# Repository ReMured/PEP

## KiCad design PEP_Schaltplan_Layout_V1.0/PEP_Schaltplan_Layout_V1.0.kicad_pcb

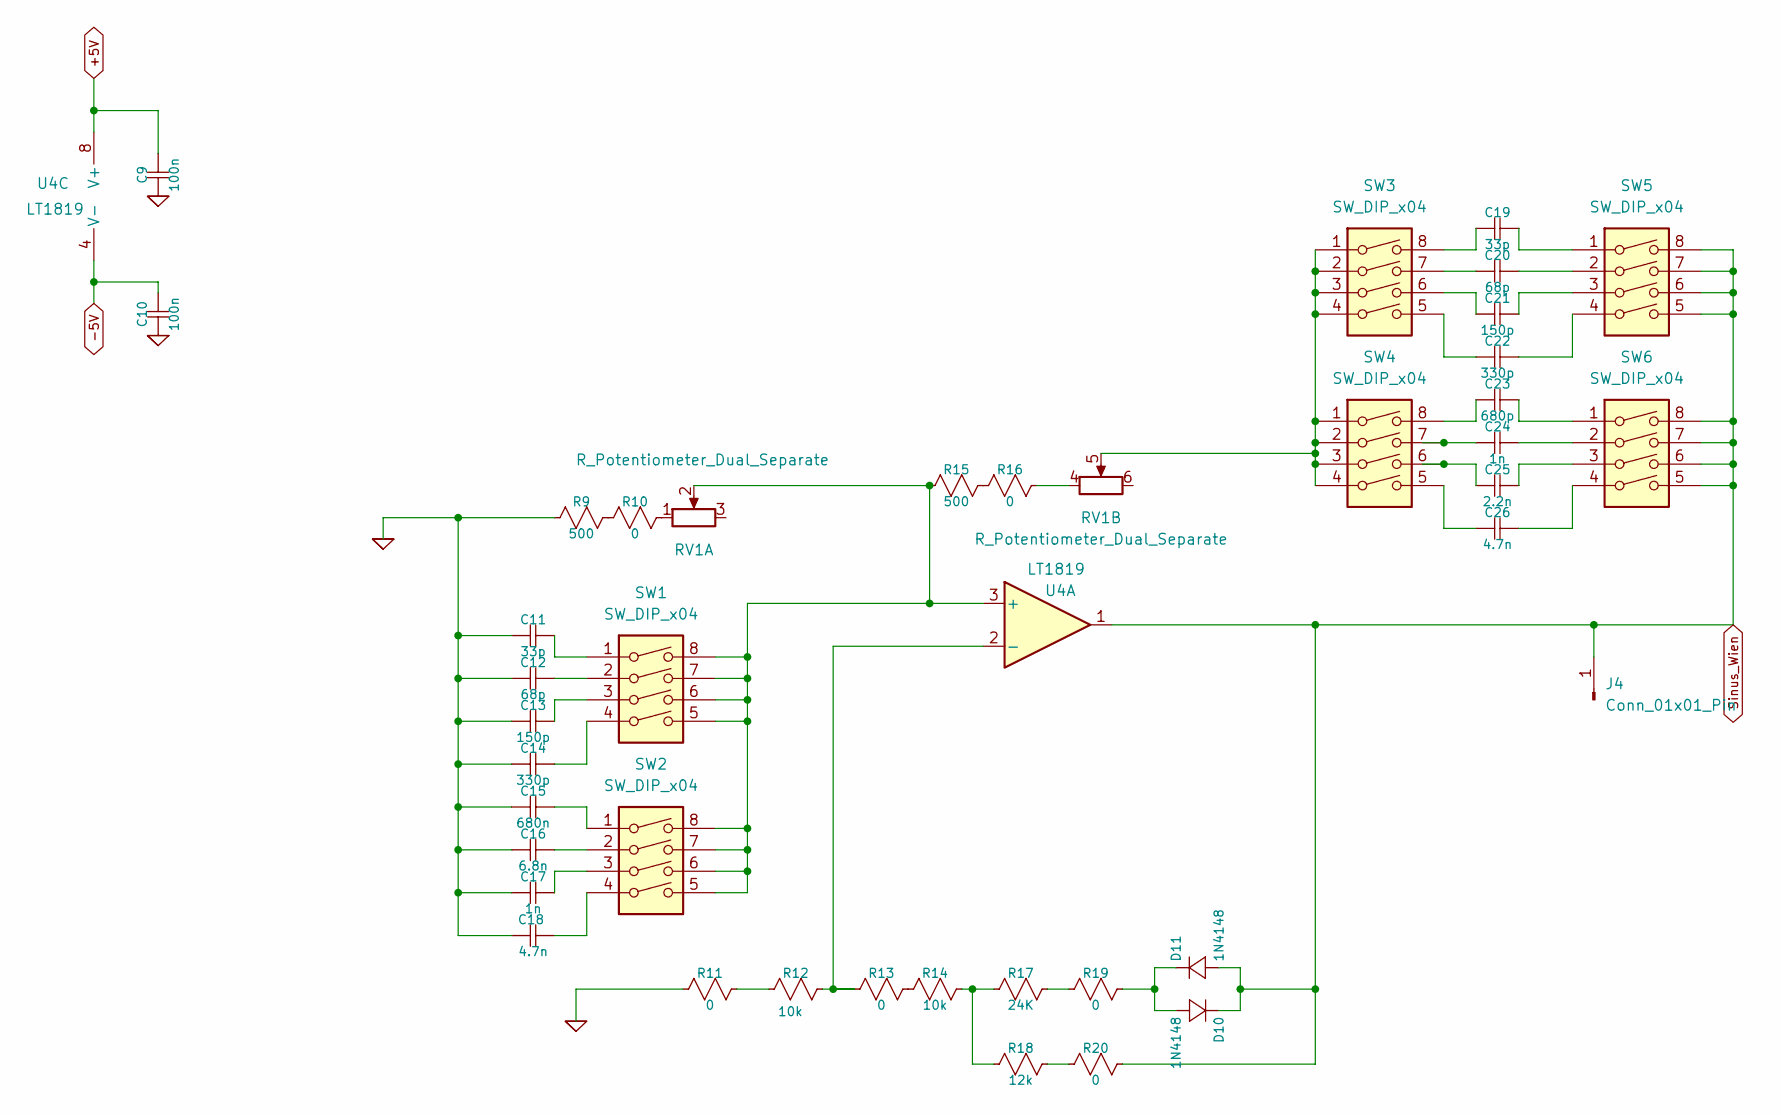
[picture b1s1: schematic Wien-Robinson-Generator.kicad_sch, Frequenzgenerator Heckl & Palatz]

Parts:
C9, C10: 100n; C_1206_3216Metric
C11, C19: 33p; C_1206_3216Metric
C12, C20: 68p; C_1206_3216Metric
C13, C21: 150p; C_1206_3216Metric
C14, C22: 330p; C_1206_3216Metric
C15: 680n; C_1206_3216Metric
C16: 6.8n; C_1206_3216Metric
C17, C24: 1n; C_1206_3216Metric
C18, C26: 4.7n; C_1206_3216Metric
C23: 680p; C_1206_3216Metric
C25: 2.2n; C_1206_3216Metric
D10, D11: 1N4148; D_DO-41_SOD81_P10.16mm_Horizontal
J4: Conn_01x01_Pin; PinSocket_1x01_P2.54mm_Vertical
R9, R15: 500; R_1206_3216Metric
R10, R11, R13, R16, R19, R20: 0; R_1206_3216Metric
R12, R14: 10k; R_1206_3216Metric
R17: 24K; R_1206_3216Metric
R18: 12k; R_1206_3216Metric
RV1: R_Potentiometer_Dual_Separate; Potentiometer_Piher_T-16H_Double_Horizontal
SW1, SW2, SW3, SW4, SW5, SW6: SW_DIP_x04; SW_DIP_SPSTx04_Slide_6.7x11.72mm_W7.62mm_P2.54mm_LowProfile
U4: LT1819; SO-8_3.9x4.9mm_P1.27mm

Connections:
+5V: C9.1, U4.8 (V+); also elsewhere on the board
-5V: C10.1, U4.4 (V-); also elsewhere on the board
GND: C9.2, C10.2, C11.2, C12.2, C13.2, C14.2, C15.2, C16.2, C17.2, C18.2, R9.2, R11.2; also elsewhere on the board
unnamed: C11.1, SW1.1
unnamed: C12.1, SW1.2
unnamed: C13.1, SW1.3
unnamed: C14.1, SW1.4
unnamed: C15.1, SW2.1
unnamed: C16.1, SW2.2
unnamed: C17.1, SW2.3
unnamed: C18.1, SW2.4
unnamed: C19.1, SW5.1
unnamed: C19.2, SW3.8
unnamed: C20.1, SW5.2
unnamed: C20.2, SW3.7
unnamed: C21.1, SW5.3
unnamed: C21.2, SW3.6
unnamed: C22.1, SW5.4
unnamed: C22.2, SW3.5
unnamed: C23.1, SW6.1
unnamed: C23.2, SW4.8
unnamed: C24.1, SW6.2
unnamed: C24.2, SW4.7
unnamed: C25.1, SW6.3
unnamed: C25.2, SW4.6
unnamed: C26.1, SW6.4
unnamed: C26.2, SW4.5
unnamed: D10.1 (+), D11.2 (-), R19.1
unnamed: R10.1, RV1.1
unnamed: R9.1, R10.2
unnamed: R11.1, R12.2
unnamed: R13.1, R14.2
unnamed: R14.1, R17.2, R18.2
unnamed: R15.1, R16.2
unnamed: R16.1, RV1.4
unnamed: R17.1, R19.2
unnamed: R18.1, R20.2
unnamed: RV1.5, SW3.1, SW3.2, SW3.3, SW3.4, SW4.1, SW4.2, SW4.3, SW4.4
unnamed: R15.2, RV1.2, SW1.5, SW1.6, SW1.7, SW1.8, SW2.5, SW2.6, SW2.7, SW2.8, U4.3 (+)
unnamed: R12.1, R13.2, U4.2 (-)
Sinus_Wien: D10.2 (-), D11.1 (+), J4.1 (Pin_1_1), R20.1, SW5.5, SW5.6, SW5.7, SW5.8, SW6.5, SW6.6, SW6.7, SW6.8, U4.1; also elsewhere on the board

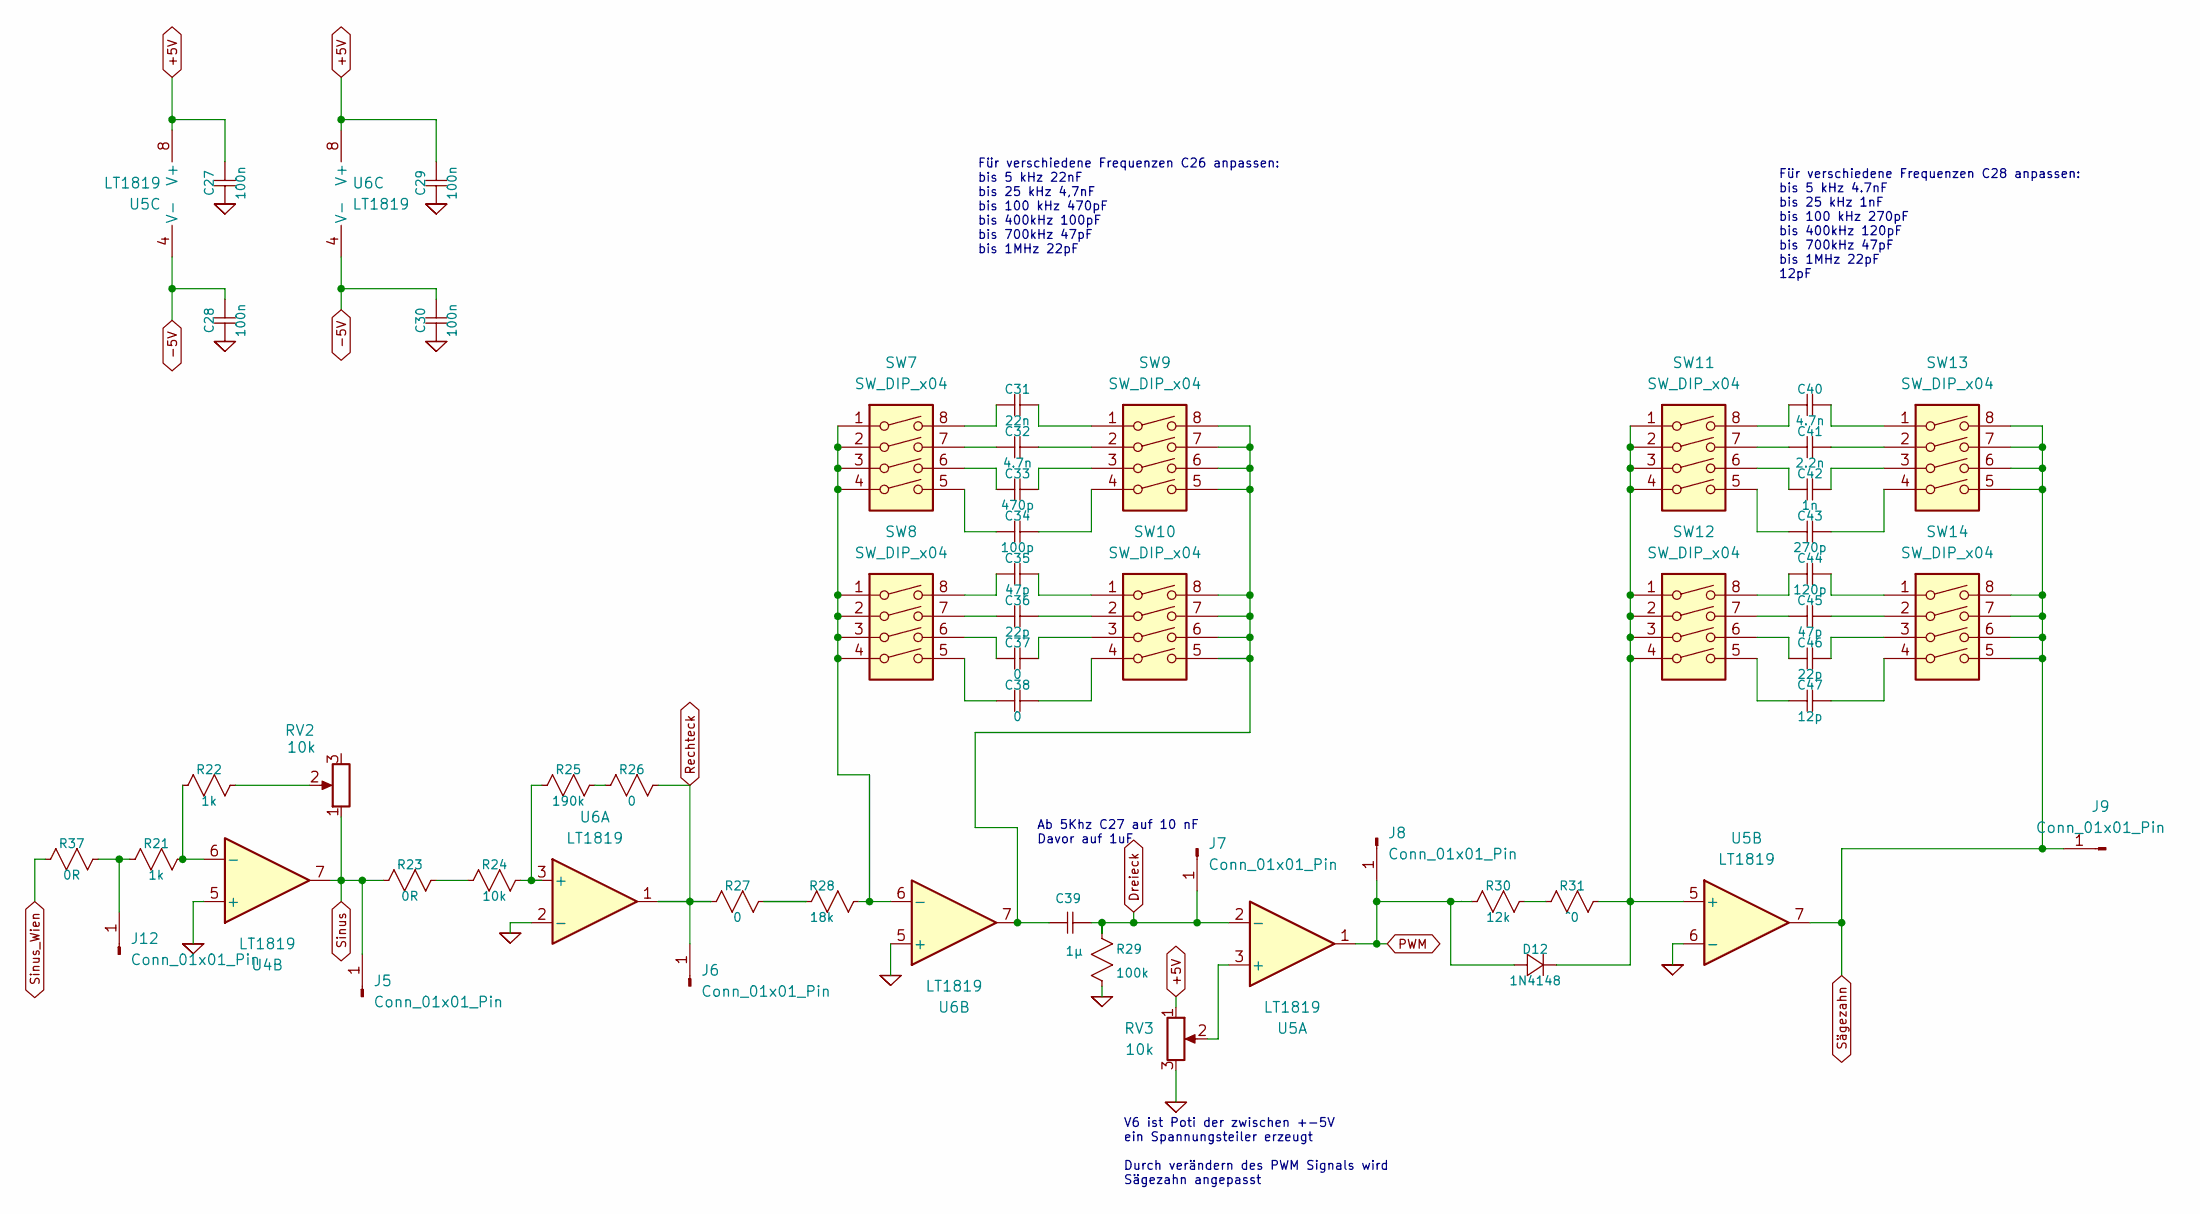
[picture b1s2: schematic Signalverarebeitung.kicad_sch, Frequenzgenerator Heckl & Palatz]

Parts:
C27, C28, C29, C30: 100n; C_1206_3216Metric
C31: 22n; C_1206_3216Metric
C32, C40: 4.7n; C_1206_3216Metric
C33: 470p; C_1206_3216Metric
C34: 100p; C_1206_3216Metric
C35, C45: 47p; C_1206_3216Metric
C36, C46: 22p; C_1206_3216Metric
C37, C38: 0; C_1206_3216Metric
C39: 1µ; C_1206_3216Metric
C41: 2.2n; C_1206_3216Metric
C42: 1n; C_1206_3216Metric
C43: 270p; C_1206_3216Metric
C44: 120p; C_1206_3216Metric
C47: 12p; C_1206_3216Metric
D12: 1N4148; D_DO-41_SOD81_P10.16mm_Horizontal
J5, J6, J7, J8, J9, J12: Conn_01x01_Pin; PinSocket_1x01_P2.54mm_Vertical
R21, R22: 1k; R_1206_3216Metric
R23, R37: 0R; R_1206_3216Metric
R24: 10k; R_1206_3216Metric
R25: 190k; R_1206_3216Metric
R26, R27: 0; R_1206_3216Metric
R28: 18k; R_1206_3216Metric
R29: 100k; R_1206_3216Metric
R30: 12k; R_1206_3216Metric
R31: ^0; R_1206_3216Metric
RV2, RV3: 10k; Potentiometer_Bourns_3266Y_Vertical
SW7, SW8, SW9, SW10, SW11, SW12, SW13, SW14: SW_DIP_x04; SW_DIP_SPSTx04_Slide_6.7x11.72mm_W7.62mm_P2.54mm_LowProfile
U4, U5, U6: LT1819; SO-8_3.9x4.9mm_P1.27mm

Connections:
+5V: C27.1, C29.1, RV3.1, U5.8 (V+), U6.8 (V+); also elsewhere on the board
-5V: C28.1, C30.1, U5.4 (V-), U6.4 (V-); also elsewhere on the board
Dreieck: C39.1, J7.1 (Pin_1_1), R29.1, U5.2 (-); also elsewhere on the board
GND: C27.2, C28.2, C29.2, C30.2, R29.2, RV3.3, U4.5 (+), U5.6 (-), U6.2 (-), U6.5 (+); also elsewhere on the board
unnamed: C31.1, SW9.1
unnamed: C31.2, SW7.8
unnamed: C32.1, SW9.2
unnamed: C32.2, SW7.7
unnamed: C33.1, SW9.3
unnamed: C33.2, SW7.6
unnamed: C34.1, SW9.4
unnamed: C34.2, SW7.5
unnamed: C35.1, SW10.1
unnamed: C35.2, SW8.8
unnamed: C36.1, SW10.2
unnamed: C36.2, SW8.7
unnamed: C37.1, SW10.3
unnamed: C37.2, SW8.6
unnamed: C38.1, SW10.4
unnamed: C38.2, SW8.5
unnamed: C39.2, SW9.5, SW9.6, SW9.7, SW9.8, SW10.5, SW10.6, SW10.7, SW10.8, U6.7
unnamed: C40.1, SW13.1
unnamed: C40.2, SW11.8
unnamed: C41.1, SW13.2
unnamed: C41.2, SW11.7
unnamed: C42.1, SW13.3
unnamed: C42.2, SW11.6
unnamed: C43.1, SW13.4
unnamed: C43.2, SW11.5
unnamed: C44.1, SW14.1
unnamed: C44.2, SW12.8
unnamed: C45.1, SW14.2
unnamed: C45.2, SW12.7
unnamed: C46.1, SW14.3
unnamed: C46.2, SW12.6
unnamed: C47.1, SW14.4
unnamed: C47.2, SW12.5
unnamed: D12.2 (-), R31.1, SW11.1, SW11.2, SW11.3, SW11.4, SW12.1, SW12.2, SW12.3, SW12.4, U5.5 (+)
unnamed: J12.1 (Pin_1_1), R21.2, R37.1
unnamed: R22.1, RV2.2
unnamed: R23.1, R24.2
unnamed: R25.1, R26.2
unnamed: R27.1, R28.2
unnamed: R30.1, R31.2
unnamed: R21.1, R22.2, U4.6 (-)
unnamed: RV3.2, U5.3 (+)
unnamed: R24.1, R25.2, U6.3 (+)
unnamed: R28.1, SW7.1, SW7.2, SW7.3, SW7.4, SW8.1, SW8.2, SW8.3, SW8.4, U6.6 (-)
PWM: D12.1 (+), J8.1 (Pin_1_1), R30.2, U5.1; also elsewhere on the board
Rechteck: J6.1 (Pin_1_1), R26.1, R27.2, U6.1; also elsewhere on the board
Sinus: J5.1 (Pin_1_1), R23.2, RV2.1, U4.7; also elsewhere on the board
Sinus_Wien: R37.2; also elsewhere on the board
Sägezahn: J9.1 (Pin_1_1), SW13.5, SW13.6, SW13.7, SW13.8, SW14.5, SW14.6, SW14.7, SW14.8, U5.7; also elsewhere on the board

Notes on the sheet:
V6 ist Poti der zwischen +-5V ein Spannungsteiler erzeugt Durch verändern des PWM Signals wird Sägezahn angepasst
Für verschiedene Frequenzen C28 anpassen: bis 5 kHz 4.7nF bis 25 kHz 1nF bis 100 kHz 270pF bis 400kHz 120pF bis 700kHz 47pF bis 1MHz 22pF 12pF
Für verschiedene Frequenzen C26 anpassen: bis 5 kHz 22nF bis 25 kHz 4,7nF bis 100 kHz 470pF bis 400kHz 100pF bis 700kHz 47pF bis 1MHz 22pF
Ab 5Khz C27 auf 10 nF Davor auf 1uF

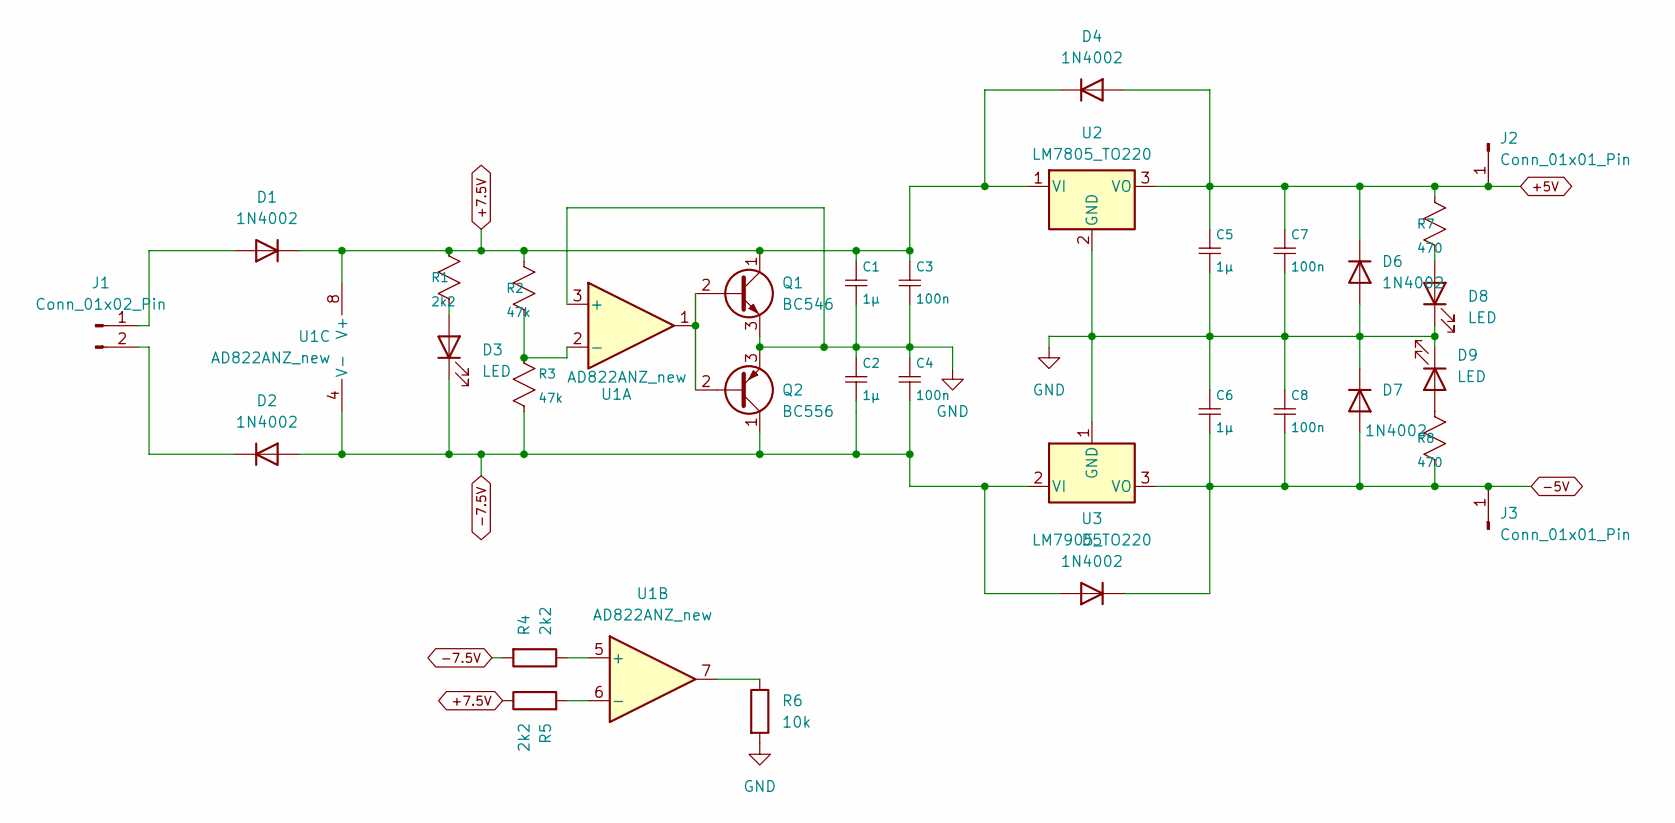
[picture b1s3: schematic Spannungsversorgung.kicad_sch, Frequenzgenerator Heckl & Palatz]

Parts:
C1, C2, C5, C6: 1µ; C_1206_3216Metric
C3, C4, C7, C8: 100n; C_1206_3216Metric
D1, D2, D4, D5, D6, D7: 1N4002; D_DO-41_SOD81_P10.16mm_Horizontal
D3, D8, D9: LED; LED_D3.0mm
J1: Conn_01x02_Pin; PinHeader_1x02_P2.54mm_Vertical
J2, J3: Conn_01x01_Pin; PinSocket_1x01_P2.54mm_Vertical
Q1: BC546; TO-92_Inline
Q2: BC556; TO-92_Inline
R1, R4, R5: 2k2; R_1206_3216Metric
R2, R3: 47k; R_1206_3216Metric
R6: 10k; R_1206_3216Metric
R7, R8: 470; R_1206_3216Metric
U1: AD822ANZ_new; DIP8
U2: LM7805_TO220; TO-220-3_Vertical
U3: LM7905_TO220; TO-220-3_Vertical

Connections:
+5V: C5.1, C7.1, D4.2 (A), D6.1 (K), J2.1 (Pin_1_1), R7.1, U2.3 (VO); also elsewhere on the board
+7.5V: C1.1, C3.1, D1.1 (K), D4.1 (K), Q1.1 (C), R1.1, R2.1, R5.1, U1.8 (V+), U2.1 (VI)
-5V: C6.2, C8.2, D5.1 (K), D7.2 (A), J3.1 (Pin_1_1), R8.2, U3.3 (VO); also elsewhere on the board
-7.5V: C2.2, C4.2, D2.2 (A), D3.1 (K), D5.2 (A), Q2.1 (C), R3.2, R4.2, U1.4 (V-), U3.2 (VI)
GND: C1.2, C2.1, C3.2, C4.1, C5.2, C6.1, C7.2, C8.1, D6.2 (A), D7.1 (K), D8.1 (K), D9.1 (K), Q1.3 (E), Q2.3 (E), R6.2, U1.3 (+), U2.2 (GND), U3.1 (GND); also elsewhere on the board
unnamed: D1.2 (A), J1.1
unnamed: D2.1 (K), J1.2
unnamed: D3.2 (A), R1.2
unnamed: D8.2 (A), R7.2
unnamed: D9.2 (A), R8.1
unnamed: Q1.2 (B), Q2.2 (B), U1.1
unnamed: R6.1, U1.7
unnamed: R2.2, R3.1, U1.2 (-)
unnamed: R4.1, U1.5 (+)
unnamed: R5.2, U1.6 (-)

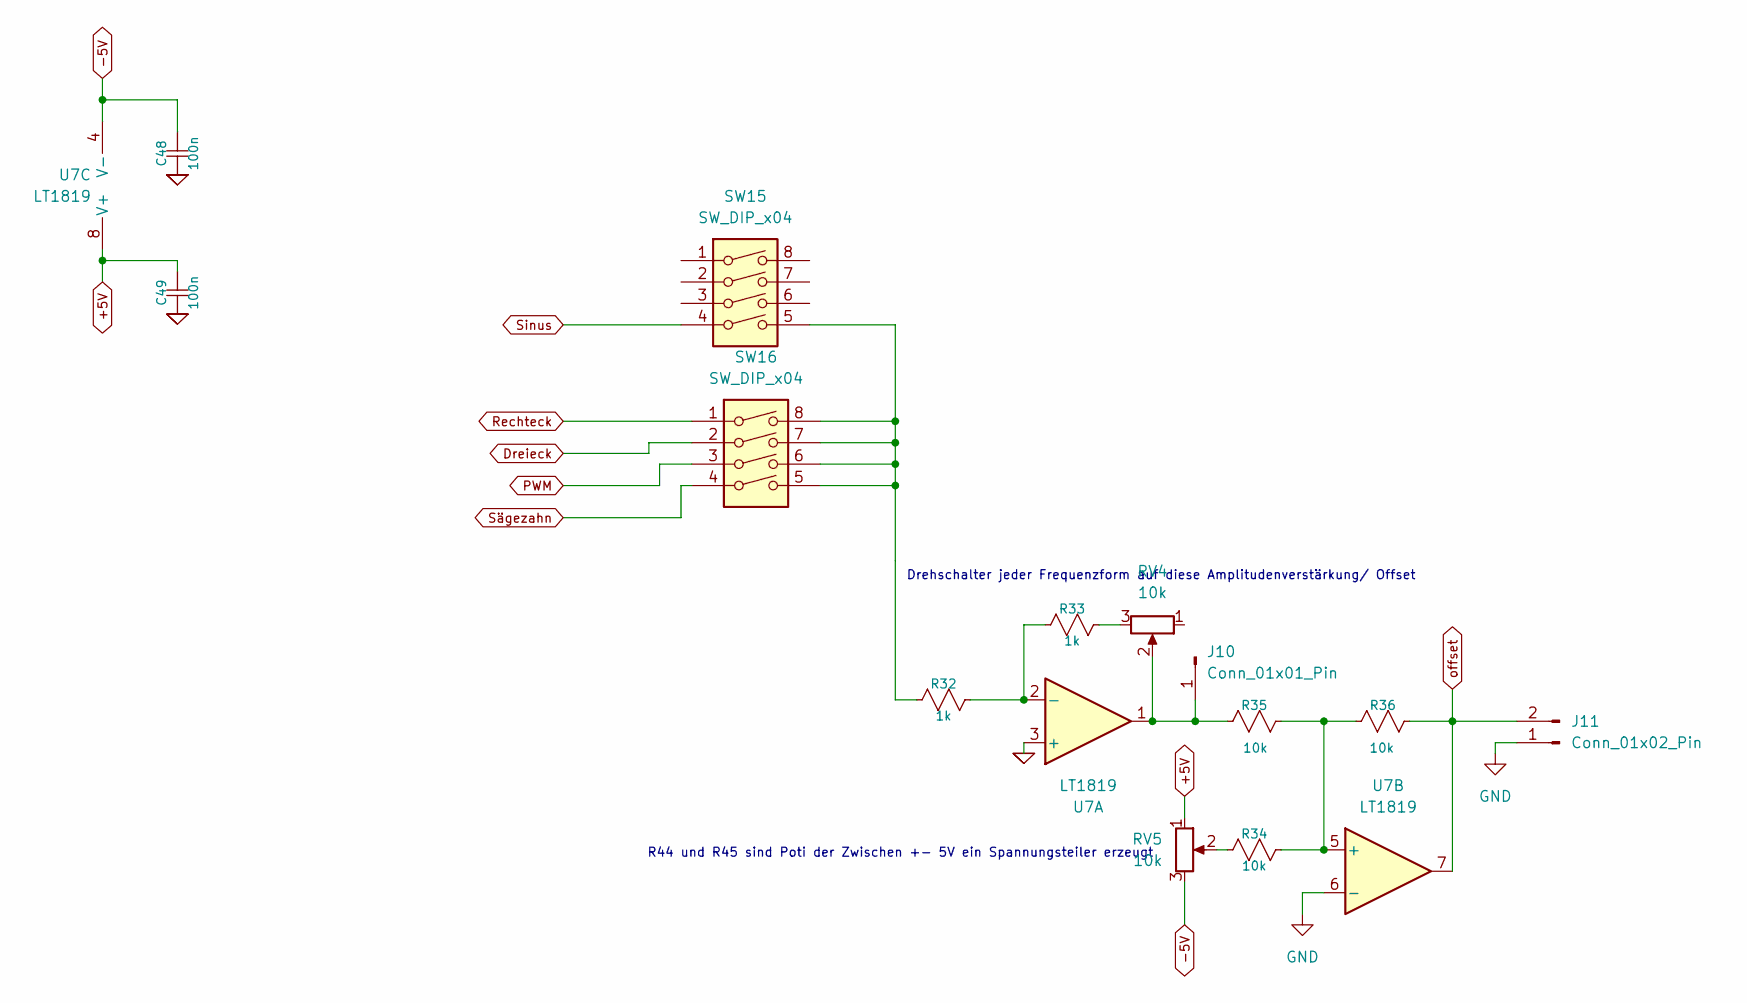
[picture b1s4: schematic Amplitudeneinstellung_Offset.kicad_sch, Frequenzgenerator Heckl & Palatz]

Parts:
C48, C49: 100n; C_1206_3216Metric
J10: Conn_01x01_Pin; PinSocket_1x01_P2.54mm_Vertical
J11: Conn_01x02_Pin; PinHeader_1x02_P2.54mm_Vertical
R32, R33: 1k; R_1206_3216Metric
R34, R35, R36: 10k; R_1206_3216Metric
RV4, RV5: 10k; Potentiometer_Bourns_3266Y_Vertical
SW15, SW16: SW_DIP_x04; SW_DIP_SPSTx04_Slide_6.7x11.72mm_W7.62mm_P2.54mm_LowProfile
U7: LT1819; SO-8_3.9x4.9mm_P1.27mm

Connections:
+5V: C49.1, RV5.1, U7.8 (V+); also elsewhere on the board
-5V: C48.1, RV5.3, U7.4 (V-); also elsewhere on the board
Dreieck: SW16.2; also elsewhere on the board
GND: C48.2, C49.2, J11.1, U7.3 (+), U7.6 (-); also elsewhere on the board
unnamed: J10.1 (Pin_1_1), R35.2, RV4.2, U7.1
unnamed: R32.2, SW15.5, SW16.5, SW16.6, SW16.7, SW16.8
unnamed: R33.1, RV4.3
unnamed: R34.1, RV5.2
unnamed: R32.1, R33.2, U7.2 (-)
unnamed: R34.2, R35.1, R36.2, U7.5 (+)
PWM: SW16.3; also elsewhere on the board
Rechteck: SW16.1; also elsewhere on the board
Sinus: SW15.4; also elsewhere on the board
Sägezahn: SW16.4; also elsewhere on the board
offset: J11.2, R36.1, U7.7

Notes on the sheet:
Drehschalter jeder Frequenzform auf diese Amplitudenverstärkung/ Offset
R44 und R45 sind Poti der Zwischen +- 5V ein Spannungsteiler erzeugt

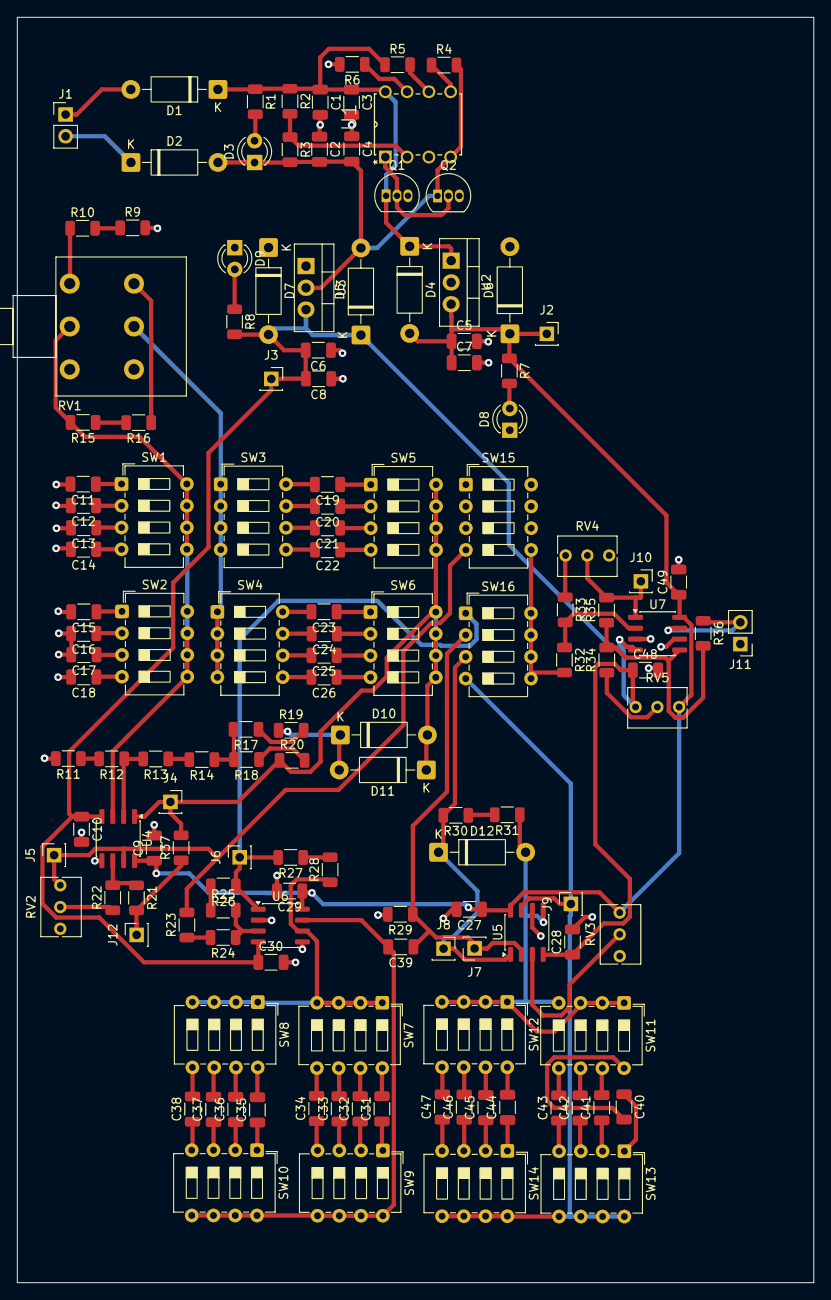
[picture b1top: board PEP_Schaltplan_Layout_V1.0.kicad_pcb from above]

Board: 2 copper layers, 92.9 x 147.6 mm, 140 parts (0 on the bottom side), 109 nets.

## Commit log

2026-04-23 hallo2
2026-04-23 Wichtige Änderung
2026-04-23 Sägezahn
2026-04-23 Möchtegernsägezahn
2026-04-23 Sägezahn-Zusatz
2026-04-23 Sägezahn-Zusatz2
2026-04-24 Sägezahnanpassung
2026-04-27 add Frequence
2026-04-28 Sägezahnaufbau final
2026-05-13 wien+ignal
2026-05-19 frequenzgaenge
2026-05-21 layout
2026-05-21 Bauoptionen1
2026-05-21 alle_Bauteile
2026-05-21 lol2
2026-05-21 Überarbeitung und Bereinigung
2026-05-22 Pinheads eingefügt, GND überall (hoffentlich angebunden)
2026-05-22 Widerstand eingefügt um Notfall Sinus extern, einzuspeisen
2026-05-22 Hab den Pin zum einspeisen vergessen
2026-05-22 Sortierung Signalverarbeitung +Offset & Amplitude
2026-05-22 ic Kondensator
2026-05-24 Leiterplatten größe definiert und erstes Auto Routing
2026-05-24 DRC Fehler Behoben
2026-05-26 Geberdaten erstellt
2026-05-26 Gerberdaten in .zip
2026-05-28 ibom aktualisiert
2026-06-11 Anpassung
2026-06-11 Fertig
2026-06-20 Upps vergessen
2026-06-25 Präsi
